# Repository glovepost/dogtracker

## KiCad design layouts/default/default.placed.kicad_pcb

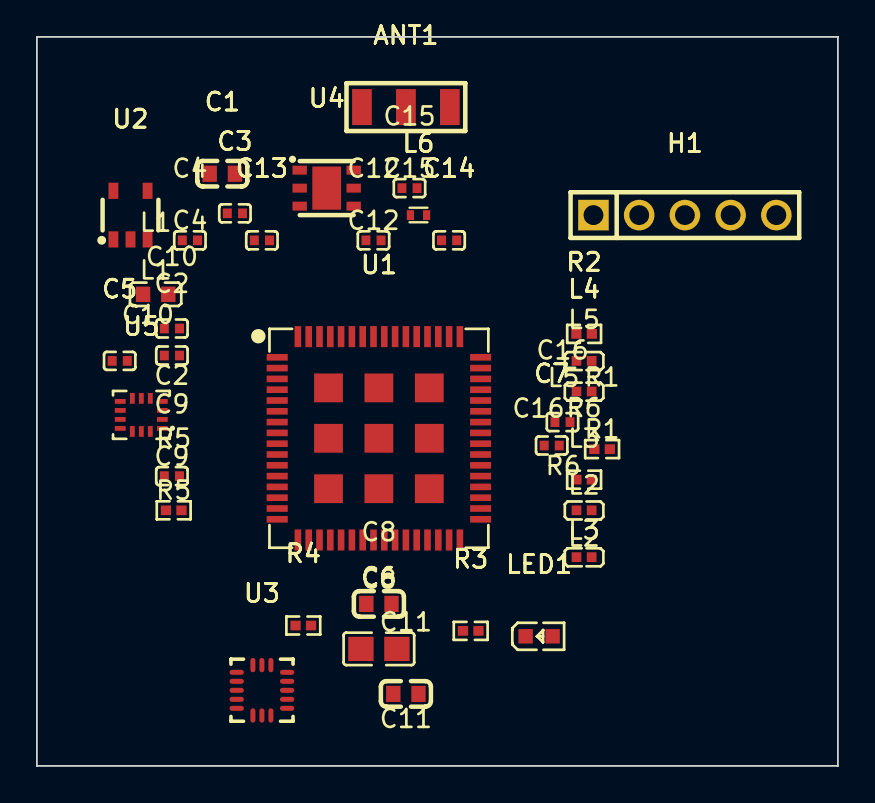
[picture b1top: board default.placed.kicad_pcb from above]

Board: 2 copper layers, 44.5 x 40.5 mm, 37 parts (1 on the bottom side), 21 nets, no tracks yet.

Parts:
ANT1: ANT-SMD_3P-L6.0-W2.0_M620720
B1: BAT-TH_CR2032-BS-6-1
C1: 10µF ±10% 10V X5R; C0603
C2, C3, C4, C5, C7, C9, C10, C12, C14: 100nF ±10% 16V X7R; C0402
C6: 22µF ±20% 25V X5R; C0805
C8, C11: 4.7µF ±10% 16V X5R; C0603
C13: 3.3pF ±2% 50V C0G; C0402
C15, C16: C0402
H1: HDR-TH_5P-P2.54-V-M
L1: 10µH ±20% 30MHz 50mA 1.17Ω; L0603
L2, L3, L4: L0402
L5: 8.2nH ±5% 3.6GHz 300mA 400mΩ; L0402
L6: 4.2nH ±2% 1.8A 44mΩ; IND-SMD_L1.0-W0.5-2
LED1: LED0603-RD
R1, R2: 4.7kΩ ±1% 62.5mW; R0402
R3: 1kΩ ±1% 62.5mW; R0402
R4, R6: 10kΩ ±1% 62.5mW; R0402
R5: R0402
U1: LGA-73_L12.0-W12.0-P0.60-TL
U2: SOT-23-5_L2.9-W1.5-P0.95-LS2.8-BL
U3: LGA-16_L3.0-W3.0-P0.50-TL
U4: WSON-6_L3.0-W3.0-P1.00-TL-EP
U5: LGA-14_L3.0-W2.5-P0.50-BR

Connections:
A: LED1.2, R3.2
Feed: ANT1.1, C15.1, L6.2
RF_OUT: L5.1, U1.37
_1: C13.1, C16.1, L5.2, L6.1
accel-int2: U1.14, U3.9
accel-vcc: C1.1, C2.1, C3.1, C4.1, C5.1, C9.1, C10.1, L4.2, U2.4, U3.1, U3.14, U4.5, U5.5, U5.8
activation: R6.2, U1.42
adc_ntc: R4.2, R5.1, U1.45
c_vcc_1-vcc: C11.1, C12.1, H1.1, L2.2, L3.1, L4.1, R1.1, R2.1, R4.1, R6.1
footprint-int2: U1.58, U5.9
gnd: ANT1.2, ANT1.3, B1.2, C1.2, C2.2, C3.2, C4.2, C5.2, C6.2, C7.2, C8.2, C9.2, C10.2, C11.2, C12.2, C13.2, C14.2, C15.2, C16.2, H1.5, LED1.1, R5.2, U1.12, U1.28, U1.35, U1.36, U1.38, U1.39, U1.46, U1.47, U1.52, U1.56, U1.65, U1.66, U1.67, U1.68, U1.69, U1.70, U1.71, U1.72, U1.73, U2.2, U2.5, U3.5, U3.7, U3.12, U4.2, U4.3, U4.7, U5.4, U5.6, U5.7
gpio_in: R3.1, U1.16
i2c_scl: R1.2, U1.8, U2.1, U3.4, U4.6, U5.13
i2c_sda: R2.2, U1.17, U2.3, U3.6, U4.1, U5.14
int1: U1.15, U3.11
int_pin: U1.19, U4.4
nrst: C14.1, H1.4, U1.44
swclk: H1.3, U1.2
swdio: H1.2, U1.1
vbat: B1.1, C6.1, L2.1, U1.4
vcc_mcu: C7.1, C8.1, L3.2, U1.3, U1.7, U1.53, U1.54, U1.55

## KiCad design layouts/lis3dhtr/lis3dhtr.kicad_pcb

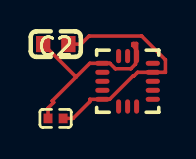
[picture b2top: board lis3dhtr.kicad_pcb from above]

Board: 2 copper layers, 3 parts (0 on the bottom side), 2 nets.

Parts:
C1: 10µF ±10% 10V X5R; C0603
C2: 100nF ±10% 16V X7R; C0402
U1: LGA-16_L3.0-W3.0-P0.50-TL

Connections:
gnd: C1.2, C2.2, U1.5, U1.12
vcc: C1.1, C2.1, U1.1, U1.14

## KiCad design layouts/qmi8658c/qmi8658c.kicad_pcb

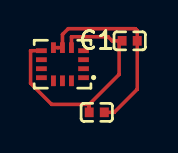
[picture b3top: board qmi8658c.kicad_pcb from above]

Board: 2 copper layers, 3 parts (0 on the bottom side), 2 nets.

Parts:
C1, C2: 100nF ±10% 16V X7R; C0402
U1: LGA-14_L3.0-W2.5-P0.50-BR

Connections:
gnd: C1.2, C2.2, U1.6, U1.7
vcc: C1.1, C2.1, U1.5, U1.8

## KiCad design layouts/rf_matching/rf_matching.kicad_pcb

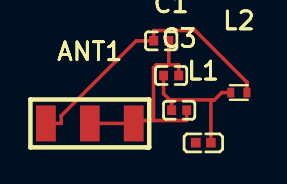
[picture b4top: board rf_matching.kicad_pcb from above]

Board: 2 copper layers, 6 parts (0 on the bottom side), 3 nets.

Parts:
ANT1: ANT-SMD_3P-L6.0-W2.0_M620720
C1: 3.3pF ±2% 50V C0G; C0402
C2, C3: C0402
L1: 8.2nH ±5% 3.6GHz 300mA 400mΩ; L0402
L2: 4.2nH ±2% 1.8A 44mΩ; IND-SMD_L1.0-W0.5-2

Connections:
Feed: ANT1.1, C2.1, L2.2
_1: C1.1, C3.1, L1.2, L2.1
gnd: ANT1.2, ANT1.3, C1.2, C2.2, C3.2

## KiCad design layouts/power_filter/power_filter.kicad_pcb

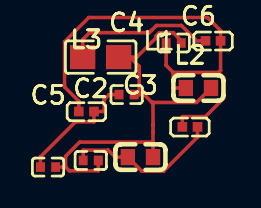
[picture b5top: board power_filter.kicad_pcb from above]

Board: 2 copper layers, 10 parts (0 on the bottom side), 5 nets.

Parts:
C1: 22µF ±20% 25V X5R; C0805
C2, C4, C5, C7: 100nF ±10% 16V X7R; C0402
C3, C6: 4.7µF ±10% 16V X5R; C0603
L1, L2, L3: L0402

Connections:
gnd: C1.2, C2.2, C3.2, C4.2, C5.2, C6.2, C7.2
vbat: C1.1, L1.1
vcc: C6.1, C7.1, L1.2, L2.1, L3.1
vcc_mcu: C2.1, C3.1, L2.2
vcc_sensors: C4.1, C5.1, L3.2

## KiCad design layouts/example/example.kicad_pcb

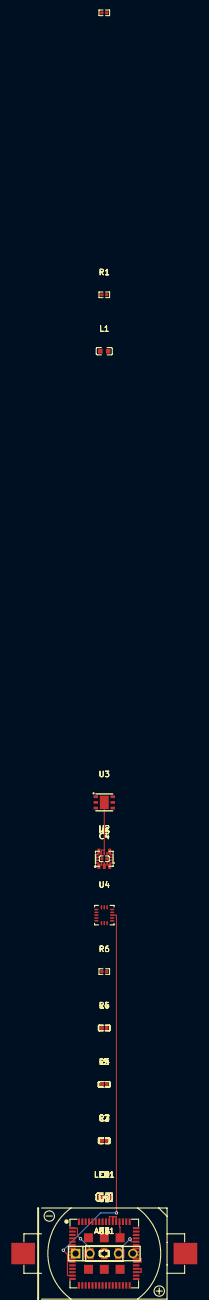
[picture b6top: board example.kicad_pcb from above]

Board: 2 copper layers, 29 parts (0 on the bottom side), 20 nets.

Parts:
ANT1: ANT-SMD_3P-L6.0-W2.0_M620720
B1: BAT-TH_CR2032-BS-6-1
C1, C2: 5.6pF 50V C0G; C0402
C3, C6: 4.7µF ±10% 10V X5R; C0402
C4, C5, C7, C8: 100nF ±10% 50V X7R; C0402
C9: 22µF ±20% 6.3V X5R; C0603
H1: HDR-TH_5P-P2.54-V-M
L1: 10µH ±20% 30MHz 50mA 1.17Ω; L0603
L2, L3, L4: L0402
L5: 4.3nH 6GHz 750mA 140mΩ; L0402
LED1: LED0603-RD
R1, R3: 10kΩ ±1% 62.5mW; R0402
R2: R0402
R4: 1kΩ ±5% 62.5mW; R0402
R5, R6: 4.7kΩ ±5% 62.5mW; R0402
U1: LGA-73_L12.0-W12.0-P0.60-TL
U2: SOT-23-5_L2.9-W1.5-P0.95-LS2.8-BL
U3: WSON-6_L3.0-W3.0-P1.00-TL-EP
U4: LGA-16_L3.0-W3.0-P0.50-TL
U5: LGA-14_L3.0-W2.5-P0.50-BR

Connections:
A: LED1.2, R4.2
DRDY_INT: U1.19, U3.4
Feed: ANT1.1, C2.1, L5.2
INT1: U1.15, U4.11
RF_OUT: C1.1, L5.1, U1.37
activation: R3.2, U1.42
adc_ntc: R1.2, R2.1, U1.45
blah-INT2-0: U1.58, U5.9
blah-INT2-1: U1.14, U4.9
blah-vcc-0: C3.1, C4.1, H1.1, L2.2, L3.1, L4.1, R1.1, R3.1, R5.1, R6.1
blah-vcc-1: C7.1, C8.1, L4.2, U2.4, U3.5, U4.1, U4.14, U5.5, U5.8
gnd: ANT1.2, ANT1.3, B1.2, C1.2, C2.2, C3.2, C4.2, C5.2, C6.2, C7.2, C8.2, C9.2, H1.5, LED1.1, R2.2, U1.12, U1.28, U1.35, U1.36, U1.38, U1.39, U1.46, U1.47, U1.52, U1.56, U1.65, U1.66, U1.67, U1.68, U1.69, U1.70, U1.71, U1.72, U1.73, U2.2, U2.5, U3.2, U3.3, U3.7, U4.5, U4.7, U4.12, U5.4, U5.6, U5.7
i2c_scl: R6.2, U1.8, U2.1, U3.6, U4.4, U5.13
i2c_sda: R5.2, U1.17, U2.3, U3.1, U4.6, U5.14
led_status: R4.1, U1.16
nrst: H1.4, U1.44
swclk: H1.3, U1.2
swdio: H1.2, U1.1
vbat: B1.1, C9.1, L2.1, U1.4
vcc_mcu: C5.1, C6.1, L3.2, U1.3, U1.7, U1.53, U1.54, U1.55

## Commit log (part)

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2026-01-10 Initial commit: AertactxDogtracker atopile design
    - Complete RAK3172-based LoRa tracker design
    - Components: LIS3DHTR, QMI8658C, HDC2080, FT24C02A EEPROM
    - CR2032 battery holder, status LED, SWD debug header
    - RF matching network with harmonic suppression
    - Reference design best practices applied (decoupling, NRST bypass)
    - 28 components with LCSC part numbers
2026-01-10 Remove unused embedded repos: OpenAllegroParser, kicad-allegro, tools/Dolphin
2026-01-10 Add RAK2270-Sticker-Tracker as submodule
2026-01-10 Add references/ to .gitignore (large files)
2026-01-13 Remove all aertactx references from project
    - Renamed aertactx_dogtracker.ato to dogtracker.ato
    - Updated module name from AertactxDogtracker to Dogtracker
    - Updated package identifier from glovepost/aertactx-dogtracker to glovepost/dogtracker
    - Renamed KiCad project files (kicad_pro, kicad_pcb, kicad_sch) to remove aertactx prefix
    - Updated all internal references in config files
